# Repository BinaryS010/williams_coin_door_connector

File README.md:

# William's Bally Coin Door Interface PCB

## Description

Simple PCB to interface William's Bally Coin Door wiring harness with virtual pinball controller (e.g. Pinscape etc).

## Credits

Design is based on an original schematic/layout by Michael Roberts (www.mjrnet.org), but adapted to parts I had on hand.

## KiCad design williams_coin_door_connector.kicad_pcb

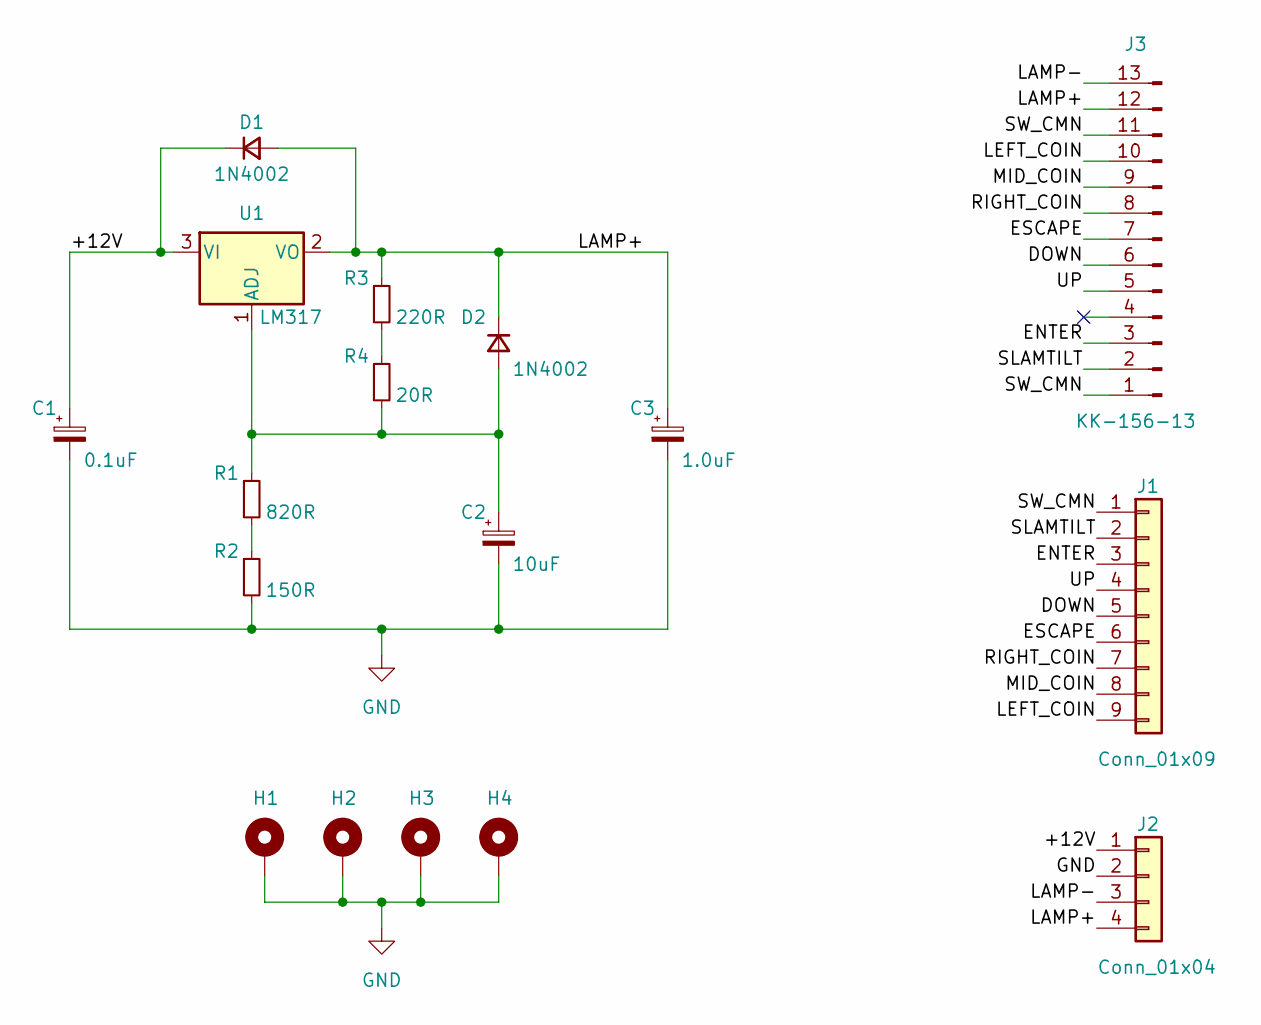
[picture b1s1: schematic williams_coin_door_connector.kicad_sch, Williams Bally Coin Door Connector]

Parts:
C1: 0.1uF; CP_Radial_D5.0mm_P2.00mm
C2: 10uF; CP_Radial_D5.0mm_P2.00mm
C3: 1.0uF; CP_Radial_D5.0mm_P2.00mm
D1, D2: 1N4002; D_DO-41_SOD81_P10.16mm_Horizontal
H1, H2, H3, H4: MountingHole_Pad; MountingHole_3.2mm_M3_DIN965_Pad
J1: Conn_01x09; PinHeader_1x09_P2.54mm_Vertical
J2: Conn_01x04; TerminalBlock_RND_205-00047_1x04_P5.00mm_Horizontal
J3: KK-156-13; Molex_KK-396_A-41791-0013_1x13_P3.96mm_Vertical
R1: 820R; R_Axial_DIN0207_L6.3mm_D2.5mm_P10.16mm_Horizontal
R2: 150R; R_Axial_DIN0207_L6.3mm_D2.5mm_P10.16mm_Horizontal
R3: 220R; R_Axial_DIN0207_L6.3mm_D2.5mm_P10.16mm_Horizontal
R4: 20R; R_Axial_DIN0207_L6.3mm_D2.5mm_P10.16mm_Horizontal
U1: LM317; TO-220-3_Vertical

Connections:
/+12V: C1.1, D1.1 (K), J2.1, U1.3 (VI)
/DOWN: J1.5, J3.6
/ENTER: J1.3, J3.3
/ESCAPE: J1.6, J3.7
/LAMP+: C3.1, D1.2 (A), D2.1 (K), J2.4, J3.12, R3.1, U1.2 (VO)
/LAMP-: J2.3, J3.13
/LEFT_COIN: J1.9, J3.10
/MID_COIN: J1.8, J3.9
/RIGHT_COIN: J1.7, J3.8
/SLAMTILT: J1.2, J3.2
/SW_CMN: J1.1, J3.1, J3.11
/UP: J1.4, J3.5
GND: C1.2, C2.2, C3.2, H1.1, H2.1, H3.1, H4.1, J2.2, R2.2
unnamed: C2.1, D2.2 (A), R1.1, R4.2, U1.1 (ADJ)
unnamed: R1.2, R2.1
unnamed: R3.2, R4.1

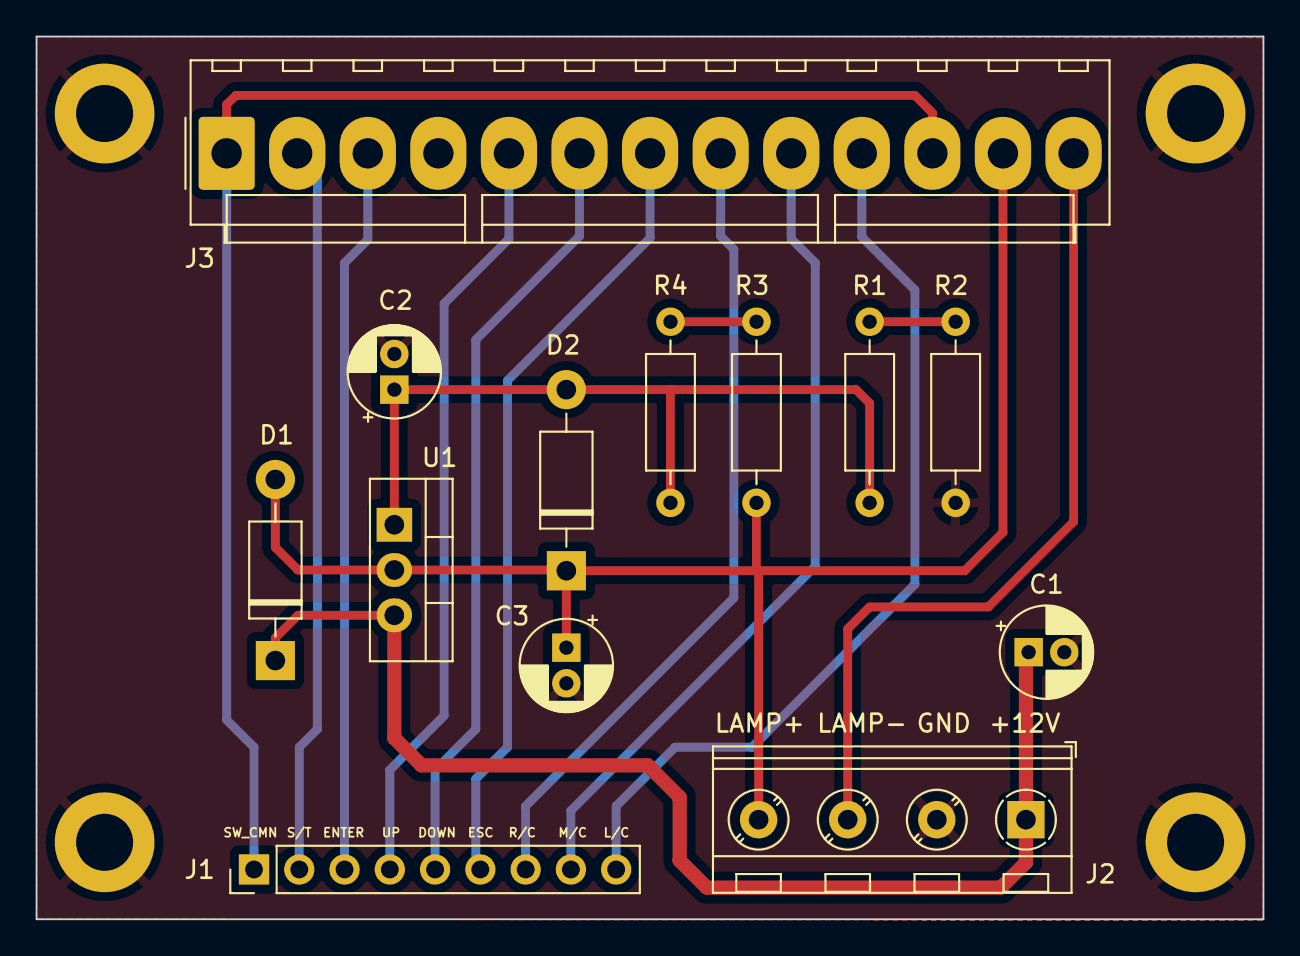
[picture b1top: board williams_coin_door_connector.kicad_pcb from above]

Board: 2 copper layers, 68.8 x 49.5 mm, 17 parts (0 on the bottom side), 16 nets.

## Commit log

2024-01-04 Initial commit.

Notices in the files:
williams_coin_door_connector.kicad_sch:
Original copyright: Michael Roberts - www.mjrnet.org
